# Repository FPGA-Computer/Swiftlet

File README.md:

This is a Personal Sonar System or the Visually Impaired Person for HaD 2015 Contest Entry.

Ver 0.0 Rel 0/	
Initial PCB release - first layout/non-tested

Ver 0.0 Rel 0.1/	
Initial PCB release - bugs fixed (so far) against Rel 0.0

  Eagle PCB/ Eagle CAD files
  Sketch3D/  Sketch3D model
  LTSpice/   Linear Tech Spice Simulation analog file

Hackaday project page is at 
https://hw-by-design.blogspot.com/2018/07/project-swiftlet-sonar-for-visually.html

This work is licensed under a Creative Commons Attribution-
NonCommercial-ShareAlike 4.0 International License.

The full detail of this license is available at: 
http://creativecommons.org/licenses/by-nc-sa/4.0/

Please contact me via hackaday.io for commercial inquiries.

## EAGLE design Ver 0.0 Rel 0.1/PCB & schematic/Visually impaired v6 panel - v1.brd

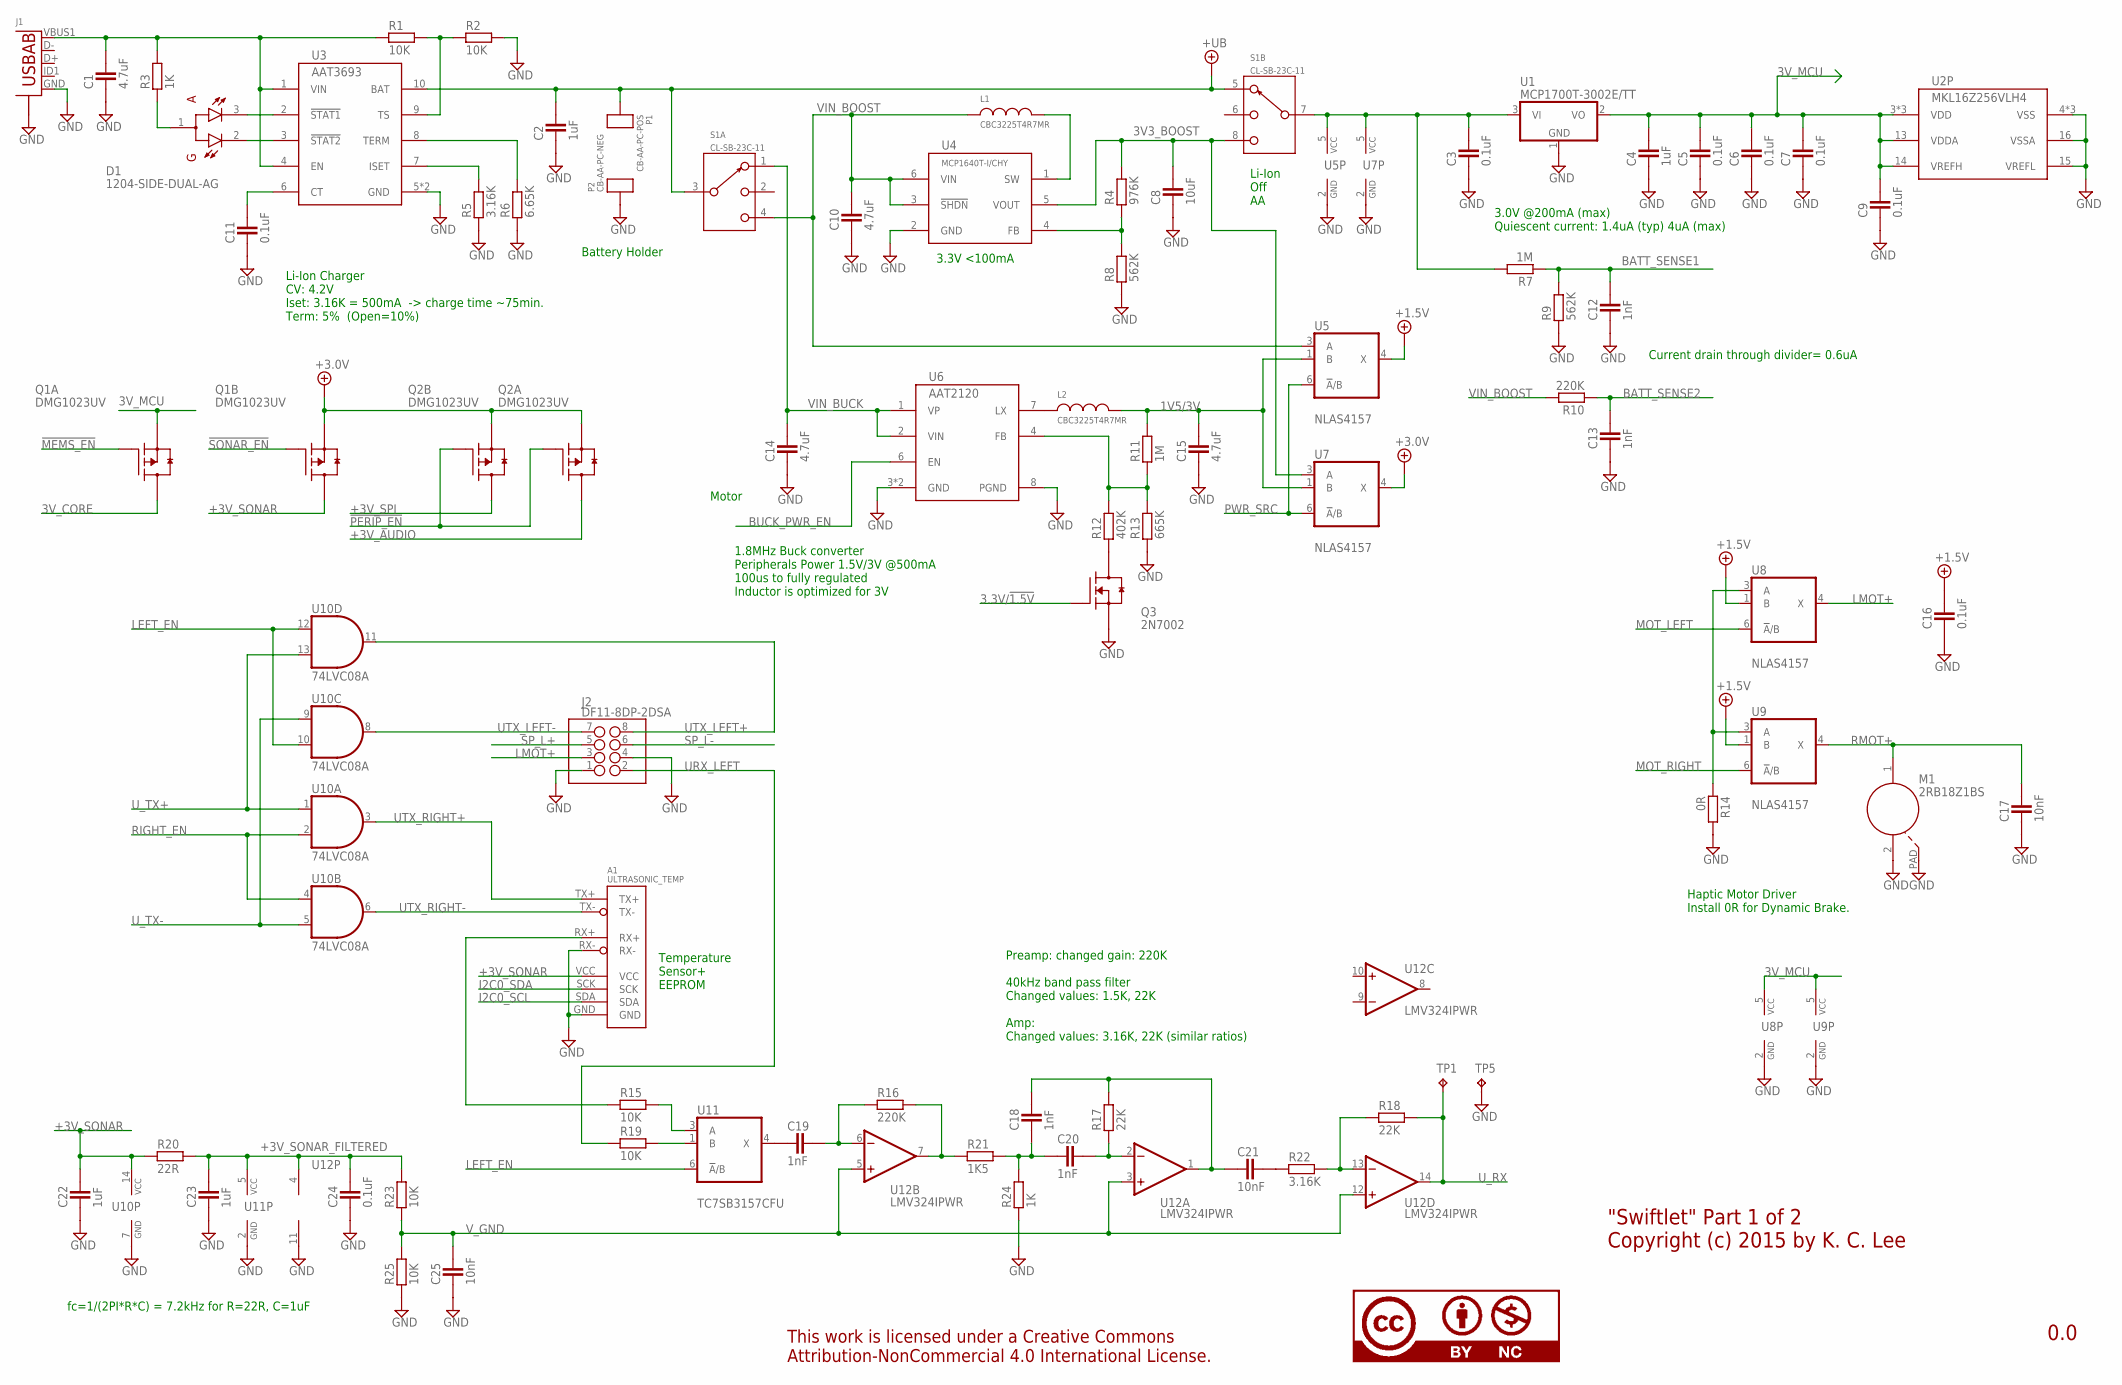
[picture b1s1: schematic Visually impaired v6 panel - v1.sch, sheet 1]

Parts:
A1: ULTRASONIC_TEMP; ULTRASONIC_ASM; PARTNO *
C1, C10, C14, C15: 4.7uF; CAPC1608X92N; PARTNO DK: 1276-2087-1-ND
C2, C22, C23: 1uF; CAPC1005X60N; PARTNO DK: 490-10435-1-ND
C3, C5, C6, C7, C9, C11, C16, C24: 0.1uF; CAPC1005X60N; PARTNO STOCK: DK 587-1227-1-ND
C4: 1uF; CAPC1608X92N; PARTNO STOCK: 1UF/10V 20% TDK
C8: 10uF; CAP2012X70N; PARTNO DK: 490-10470-1-ND
C12, C13, C18, C19, C20: 1nF; CAPC1005X60N; PARTNO DK: 490-6349-1-ND
C17, C21, C25: 10nF; CAPC1005X60N; PARTNO DK: 490-1312-1-ND
D1: 1204-SIDE-DUAL-AG; LED_1204; PARTNO STOCK
J1: USB-ABBG; USB-AB-MICRO-SMD_V03_SF; PARTNO DX: SKU134132
J2: DF11-8DP-2DSA; PARTNO DK: H10231-ND
L1, L2: CBC3225T4R7MR; INDC3225X135N; PARTNO DK: 587-1624-1-ND
M1: 2RB18Z1BS; PARTNO ALIEXPRESS
P1: CB-AA-PC-POS; PARTNO DK: CB-AA-PC-POS-ND
P2: CB-AA-PC-NEG; PARTNO DK: CB-AA-PC-NEG-ND
Q1, Q2: DMG1023UV; SOT563; PARTNO DK: DMG1023UV-7DICT-ND
Q3: 2N7002; SOT95P280X135-3N; PARTNO STOCK
R1, R2, R15, R19, R23, R25: 10K; RESC1005X40AN; PARTNO DK: 311-10.0KLRCT-ND
R3, R24: 1K; RESC1005X40AN; PARTNO DK: 311-1.00KLRCT-ND
R4: 976K; RESC1005X40AN; PARTNO DK: 1276-4289-1-ND
R5, R22: 3.16K; RESC1005X40AN; PARTNO DK: 1276-4063-1-ND
R6: 6.65K; RESC1005X40AN; PARTNO DK: 1276-4097-1-ND
R7, R11: 1M; RESC1005X40AN; PARTNO DK: 311-1.00MLRCT-ND
R8, R9: 562K; RESC1005X40AN; PARTNO DK: 1276-4268-1-ND
R10, R16: 220K; RESC1005X40AN; PARTNO DK: 311-220KLRCT-ND
R12: 402K; RESC1005X40AN; PARTNO DK: 1276-4254-1-ND
R13: 665K; RESC1005X40AN; PARTNO DK: 1276-4275-1-ND
R14: 0R; RESC1005X40AN; PARTNO DK: 311-0.0JRCT-ND
R17, R18: 22K; RESC1005X40AN; PARTNO DK: 311-22.0KLRCT-ND
R20: 22R; RESC1005X40AN; PARTNO DK: 311-22.0LRCT-ND
R21: 1K5; RESC1005X40AN; PARTNO DK: 311-1.50KLRCT-ND
S1: CL-SB-23C-11; SW-JS203011AQN; PARTNO DK: 563-1360-ND
TP1, TP5: TPTP06SQ; TP06SQ; PARTNO *
U1: MCP1700T-3002E/TT; SOT95P280X135-3N; PARTNO STOCK: MCP1700T-3002E/TTCT-ND
U2: MKL16Z256VLH4; LQFP64; PARTNO DK: MKL16Z256VLH4-ND
U3: AAT3693; TDFN-10; PARTNO DK: 863-1512-1-ND
U4: MCP1640T-I/CHY; SOT26; PARTNO DK: MCP1640T-I/CHYCT-ND
U5, U7, U8, U9: NLAS4157; DCK_R-PDSO-G6; PARTNO DK: NLAS4157DFT2GOSCT-ND
U6: AAT2120; STDFN22-8; PARTNO DK: 863-1527-1-ND
U10: 74LVC08A; TSSOP14; PARTNO DK: 296-1221-1-ND
U11: TC7SB3157CFU; DCK_R-PDSO-G6; PARTNO DK: TC7SB3157CFULFCT-ND
U12: LMV324IPWR; TSSOP14; PARTNO DK: LMV324TSG-13DICT-ND
U$1: CC100%; CC-100; PARTNO *

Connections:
1V5/3V: C15.2, L2.2, R11.2, U5.1 (B), U7.1 (B)
3.3V/!1.5V: Q3.1 (G); also elsewhere on the board
3V3_BOOST: C8.2, R4.2, S1.8 (3), U4.5 (VOUT), U7.3 (A)
3V_CORE: Q1.P$6 (D); also elsewhere on the board
3V_MCU: C4.2, C5.2, C6.2, C7.2, C9.2, Q1.P$1 (S), U1.2 (VO), U2.3 (VDD), U2.13 (VDDA), U2.14 (VREFH), U2.30 (VDD), U2.48 (VDD), U8.5 (VCC), U9.5 (VCC); also elsewhere on the board
!MEMS_EN: Q1.P$2 (G); also elsewhere on the board
!PERIP_EN: Q2.P$2 (G), Q2.P$5 (G); also elsewhere on the board
!SONAR_EN: Q1.P$5 (G); also elsewhere on the board
+1.5V: C16.2, U5.4 (X), U8.1 (B), U9.1 (B)
+3.0V: Q1.P$4 (S), Q2.P$1 (S), Q2.P$4 (S), U7.4 (X); also elsewhere on the board
+3V_AUDIO: Q2.P$6 (D); also elsewhere on the board
+3V_SONAR: A1.VCC, C22.2, Q1.P$3 (D), R20.1, U10.14 (VCC)
+3V_SONAR_FILTERED: C23.2, C24.2, R20.2, R23.2, U11.5 (VCC), U12.4 (V+)
+3V_SPI: Q2.P$3 (D); also elsewhere on the board
+UB: C2.2, P1.1, S1.3 (S), S1.5 (1), U3.10 (BAT)
BATT_SENSE1: C12.2, R7.1, R9.2; also elsewhere on the board
BATT_SENSE2: C13.2, R10.1; also elsewhere on the board
BUCK_PWR_EN: U6.6 (EN); also elsewhere on the board
GND: A1.GND, A1.RX-, C1.1, C2.1, C3.1, C4.1, C5.1, C6.1, C7.1, C8.1, C9.1, C10.1, C11.1, C12.1, C13.1, C14.1, C15.1, C16.1, C17.1, C22.1, C23.1, C24.1, C25.1, J1.GND, J1.S1 (S), J1.S2 (S), J1.S3 (S), J1.S4 (S), J2.1, J2.4, M1.2, M1.PAD, P2.1, P2.2, Q3.2 (S), R2.2, R5.1, R6.1, R8.1, R9.1, R13.1, R14.2, R24.1, R25.1, TP5.TP, U1.1 (GND), U2.4 (VSS), U2.15 (VREFL), U2.16 (VSSA), U2.31 (VSS), U2.47 (VSS), U3.5 (GND), U3.EP (GND), U4.2 (GND), U5.2 (GND), U6.3 (GND), U6.8 (PGND), U6.PAD (GND), U7.2 (GND), U8.2 (GND), U9.2 (GND), U10.7 (GND), U11.2 (GND), U12.11 (V-); also elsewhere on the board
I2C0_SCL: A1.SDA; also elsewhere on the board
I2C0_SDA: A1.SCK; also elsewhere on the board
LEFT_EN: U10.10 (I1), U10.12 (I0), U11.6 (!A!/B); also elsewhere on the board
LMOT+: J2.3, U8.4 (X)
MOT_LEFT: U8.6 (!A!/B); also elsewhere on the board
MOT_RIGHT: U9.6 (!A!/B); also elsewhere on the board
unnamed: A1.RX+, R15.1
unnamed: R14.1, U8.3 (A), U9.3 (A)
unnamed: L1.2, U4.1 (SW)
unnamed: C11.2, U3.6 (CT)
unnamed: R5.2, U3.7 (ISET)
unnamed: R6.2, U3.8 (TERM)
unnamed: D1.1 (A), R3.1
unnamed: D1.3 (C1), U3.2 (!STAT1)
unnamed: D1.2 (C2), U3.3 (!STAT2)
unnamed: C1.2, J1.VBUS1 (VBUS), R1.1, R3.2, U3.1 (VIN), U3.4 (EN)
unnamed: R1.2, R2.1, U3.9 (TS)
unnamed: C21.2, R22.1
unnamed: R19.2, U11.1 (B)
unnamed: R18.1, R22.2, U12.13 (-IN)
unnamed: C19.2, R16.1, U12.6 (-IN)
unnamed: R16.2, R21.1, U12.7 (OUT)
unnamed: C18.1, C20.1, R21.2, R24.2
unnamed: C20.2, R17.1, U12.2 (-IN)
unnamed: R15.2, U11.3 (A)
unnamed: C19.1, U11.4 (X)
unnamed: R4.1, R8.2, U4.4 (FB)
unnamed: L2.1, U6.7 (LX)
unnamed: R11.1, R12.2, R13.2, U6.4 (FB)
unnamed: Q3.3 (D), R12.1
PWR_SRC: U5.6 (!A!/B), U7.6 (!A!/B); also elsewhere on the board
RIGHT_EN: U10.2 (I1), U10.4 (I0); also elsewhere on the board
RMOT+: C17.2, M1.1, U9.4 (X)
SP_L+: J2.5; also elsewhere on the board
SP_L-: J2.6; also elsewhere on the board
URX_LEFT: J2.2, R19.1
UTX_LEFT+: J2.8, U10.11 (O)
UTX_LEFT-: J2.7, U10.8 (O)
UTX_RIGHT+: A1.TX+, U10.3 (O)
UTX_RIGHT-: A1.TX-, U10.6 (O)
U_RX: R18.2, TP1.TP, U12.14 (OUT); also elsewhere on the board
U_RX__: C18.2, C21.1, R17.2, U12.1 (OUT)
U_TX+: U10.1 (I0), U10.13 (I1); also elsewhere on the board
U_TX-: U10.5 (I1), U10.9 (I0); also elsewhere on the board
VIN_BOOST: C10.2, L1.1, R10.2, S1.4 (3), U4.3 (!SHDN), U4.6 (VIN), U5.3 (A)
VIN_BUCK: C14.2, S1.1, U6.1 (VP), U6.2 (VIN)
VIN_MCU: C3.2, R7.2, S1.7 (S), U1.3 (VI), U5.5 (VCC), U7.5 (VCC)
V_GND: C25.2, R23.1, R25.2, U12.3 (+IN), U12.5 (+IN), U12.12 (+IN)

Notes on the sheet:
Li-Ion Off AA
3.3V <100mA
Li-Ion Charger CV: 4.2V Iset: 3.16K = 500mA -> charge time ~75min. Term: 5% (Open=10%)
3.0V @200mA (max) Quiescent current: 1.4uA (typ) 4uA (max)
Motor
Battery Holder
Preamp: changed gain: 220K 40kHz band pass filter Changed values: 1.5K, 22K Amp: Changed values: 3.16K, 22K (similar ratios)
1.8MHz Buck converter Peripherals Power 1.5V/3V @500mA 100us to fully regulated Inductor is optimized for 3V
Temperature Sensor+ EEPROM
Haptic Motor Driver Install 0R for Dynamic Brake.
fc=1/(2PI*R*C) = 7.2kHz for R=22R, C=1uF
"Swiftlet" Part 1 of 2 Copyright (c) 2015 by K. C. Lee
0.0
Current drain through divider= 0.6uA

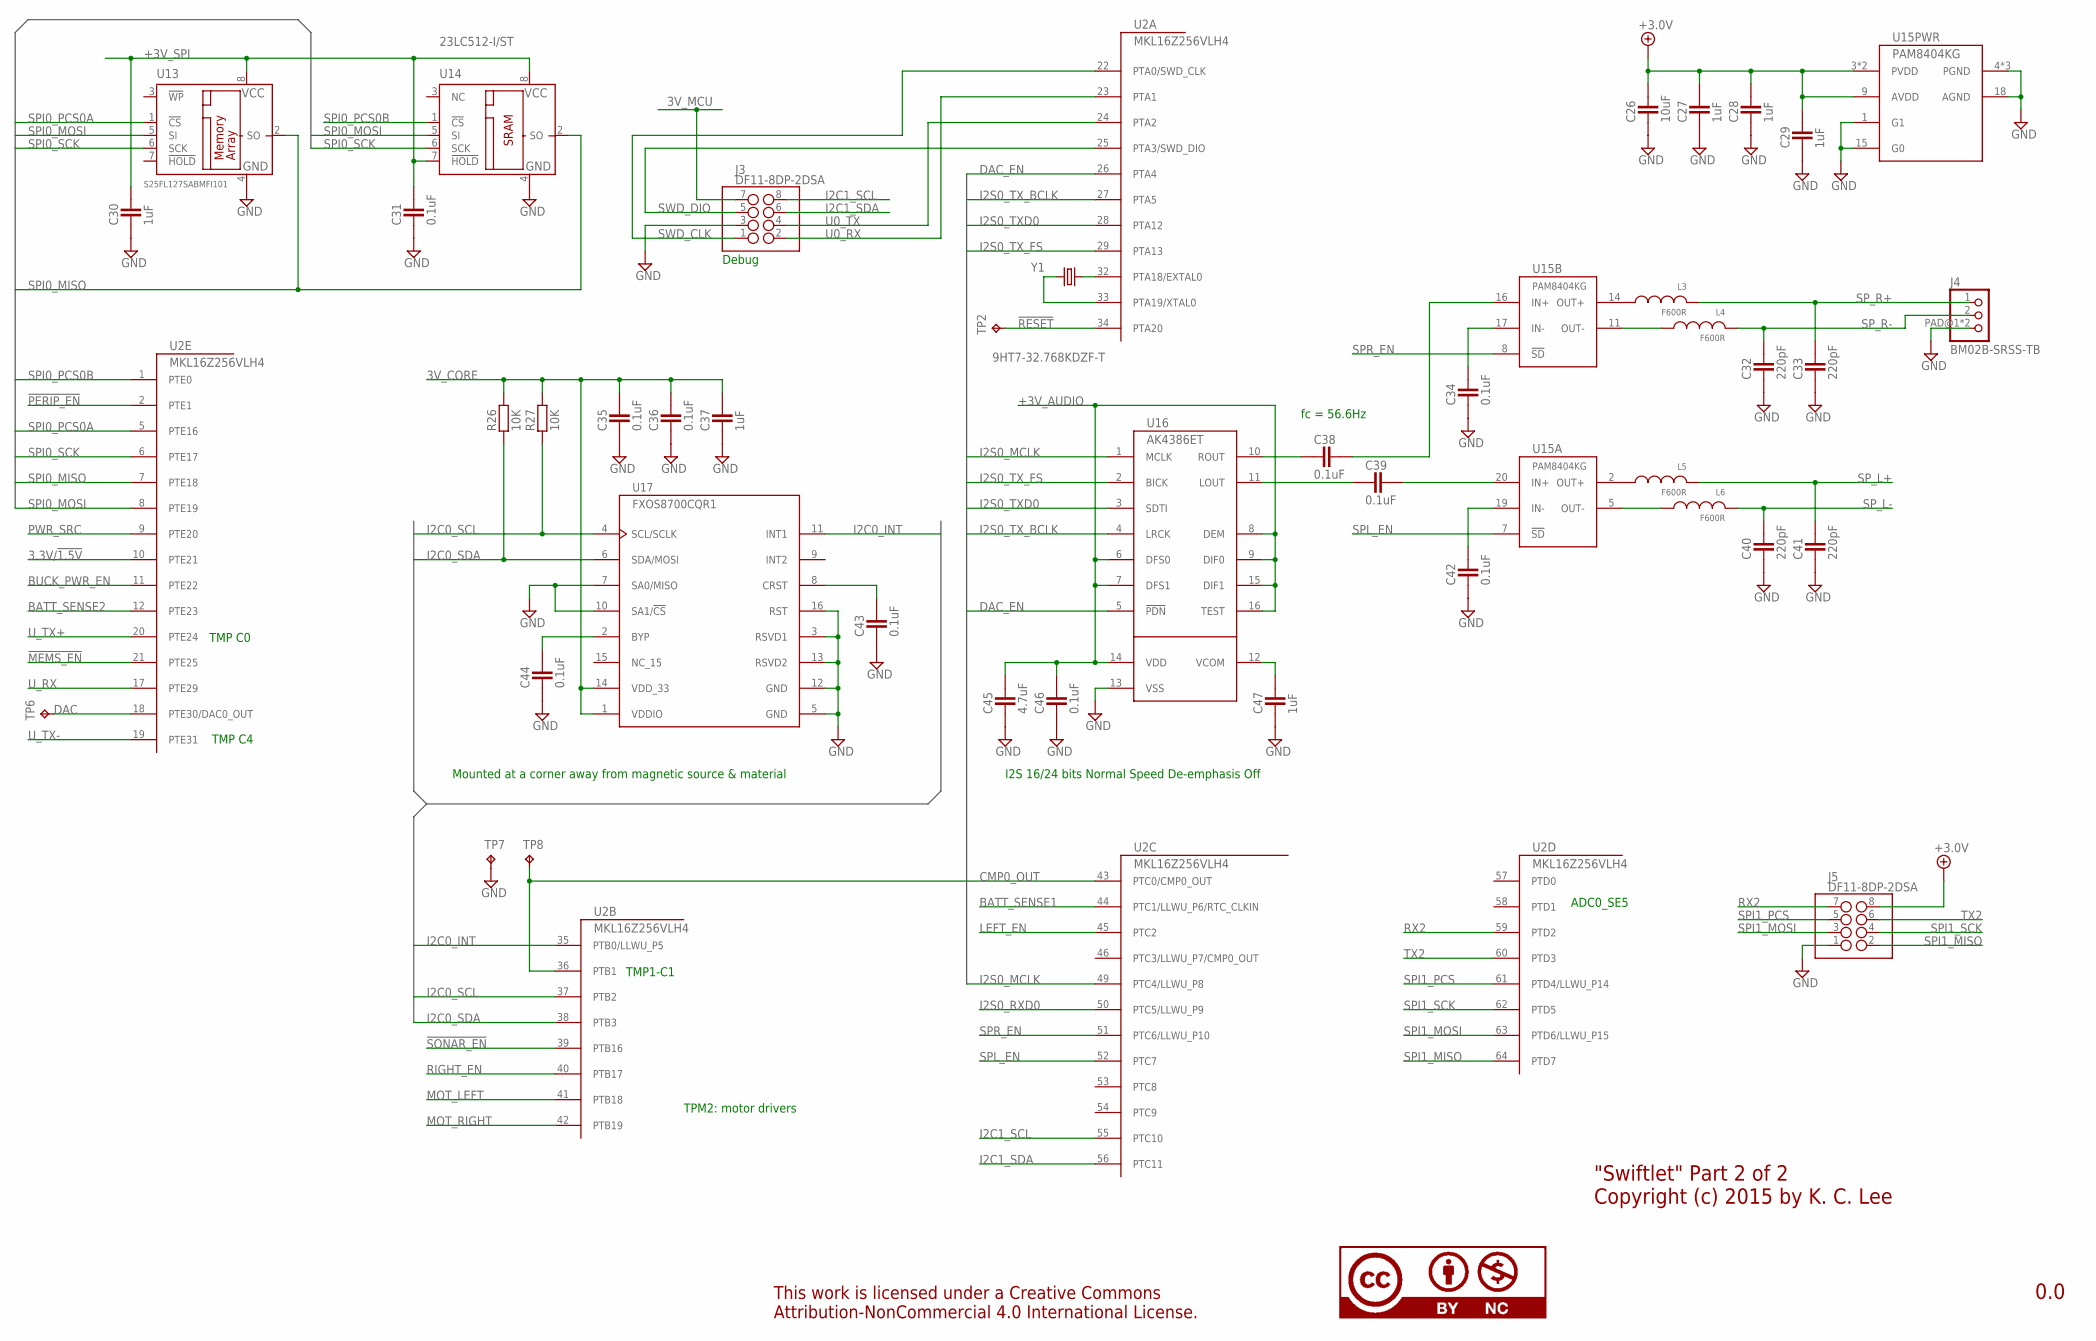
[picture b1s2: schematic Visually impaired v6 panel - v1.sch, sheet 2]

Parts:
C26: 10uF; CAP2012X70N; PARTNO DK: 490-10470-1-ND
C27, C28, C29, C30, C37, C47: 1uF; CAPC1005X60N; PARTNO DK: 490-10435-1-ND
C31, C34, C35, C36, C38, C39, C42, C43, C44, C46: 0.1uF; CAPC1005X60N; PARTNO STOCK: DK 587-1227-1-ND
C32, C33, C40, C41: 220pF; CAPC1005X60N; PARTNO DK: 1276-1531-1-ND
C45: 4.7uF; CAPC1608X92N; PARTNO DK: 1276-2087-1-ND
J3, J5: DF11-8DP-2DSA; PARTNO DK: H10231-ND
J4: BM02B-SRSS-TB; PARTNO *
L3, L4, L5, L6: F600R; INDC1005X60N; PARTNO DK: 553-2374-1-ND
R26, R27: 10K; RESC1005X40AN; PARTNO DK: 311-10.0KLRCT-ND
TP2, TP6, TP7, TP8: TPTP06SQ; TP06SQ; PARTNO *
U2: MKL16Z256VLH4; LQFP64; PARTNO DK: MKL16Z256VLH4-ND
U13: S25FL127SABMFI101; S0C008; PARTNO STOCK: DK 1274-1045-ND
U14: 23LC512-I/ST; TSSOP8; PARTNO DK: 23LC512-I/ST-ND
U15: PAM8404KG; QFN4040-20; PARTNO DK: PAM8404KGRDICT-ND
U16: AK4386ET; TSSOP16; PARTNO DK: 974-1010-1-ND
U17: FXOS8700CQR1; QFN16_0P5_3X3; PARTNO DK: FXOS8700CQR1CT-ND
U$3: CC100%; CC-100; PARTNO *
Y1: 9HT7-32.768KDZF-T; 9HT7; PARTNO DK: 887-1860-1-ND

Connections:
3.3V/!1.5V: U2.10 (PTE21); also elsewhere on the board
3V_CORE: C35.2, C36.2, C37.2, R26.2, R27.2, U17.1 (VDDIO), U17.14 (VDD_33); also elsewhere on the board
3V_MCU: J3.7; also elsewhere on the board
!MEMS_EN: U2.21 (PTE25); also elsewhere on the board
!PERIP_EN: U2.2 (PTE1); also elsewhere on the board
!RESET: TP2.TP, U2.34 (PTA20)
!SONAR_EN: U2.39 (PTB16); also elsewhere on the board
+3.0V: C26.2, C27.2, C28.2, C29.2, J5.8, U15.3 (PVDD), U15.9 (AVDD), U15.13 (PVDD); also elsewhere on the board
+3V_AUDIO: C45.2, C46.2, U16.6 (DFS0), U16.7 (DFS1), U16.8 (DEM), U16.9 (DIF0), U16.14 (VDD), U16.15 (DIF1), U16.16 (TEST); also elsewhere on the board
+3V_SPI: C30.2, C31.2, U13.8 (VCC), U14.7 (!HOLD), U14.8 (VCC); also elsewhere on the board
BATT_SENSE1: U2.44 (PTC1/LLWU_P6/RTC_CLKIN); also elsewhere on the board
BATT_SENSE2: U2.12 (PTE23); also elsewhere on the board
BUCK_PWR_EN: U2.11 (PTE22); also elsewhere on the board
BYP: C44.2, U17.2 (BYP)
CMP0_OUT: TP8.TP, U2.36 (PTB1), U2.43 (PTC0/CMP0_OUT)
CRST: C43.2, U17.8 (CRST)
DAC: TP6.TP, U2.18 (PTE30/DAC0_OUT)
DAC_EN: U2.26 (PTA4), U16.5 (!PDN)
GND: C26.1, C27.1, C28.1, C29.1, C30.1, C31.1, C32.1, C33.1, C34.1, C35.1, C36.1, C37.1, C40.1, C41.1, C42.1, C43.1, C44.1, C45.1, C46.1, C47.1, J3.3, J4.PAD@1 (3), J4.PAD@2 (3), J5.1, TP7.TP, U13.4 (GND), U14.4 (GND), U15.1 (G1), U15.4 (PGND), U15.12 (PGND), U15.15 (G0), U15.18 (AGND), U15.PAD (PGND), U16.13 (VSS), U17.3 (RSVD1), U17.5 (GND), U17.7 (SA0/MISO), U17.10 (SA1/!CS), U17.12 (GND), U17.13 (RSVD2), U17.16 (RST); also elsewhere on the board
I2C0_INT: U2.35 (PTB0/LLWU_P5), U17.11 (INT1)
I2C0_SCL: R27.1, U2.37 (PTB2), U17.4 (SCL/SCLK); also elsewhere on the board
I2C0_SDA: R26.1, U2.38 (PTB3), U17.6 (SDA/MOSI); also elsewhere on the board
I2C1_SCL: J3.8, U2.55 (PTC10)
I2C1_SDA: J3.6, U2.56 (PTC11)
I2S0_MCLK: U2.49 (PTC4/LLWU_P8), U16.1 (MCLK)
I2S0_RXD0: U2.50 (PTC5/LLWU_P9)
I2S0_TXD0: U2.28 (PTA12), U16.3 (SDTI)
I2S0_TX_BCLK: U2.27 (PTA5), U16.4 (LRCK)
I2S0_TX_FS: U2.29 (PTA13), U16.2 (BICK)
LEFT_EN: U2.45 (PTC2); also elsewhere on the board
MOT_LEFT: U2.41 (PTB18); also elsewhere on the board
MOT_RIGHT: U2.42 (PTB19); also elsewhere on the board
unnamed: U2.32 (PTA18/EXTAL0), Y1.1
unnamed: U2.33 (PTA19/XTAL0), Y1.4 (2)
unnamed: C34.2, U15.17 (IN-)
unnamed: C47.2, U16.12 (VCOM)
unnamed: C42.2, U15.19 (IN-)
unnamed: C38.1, U16.10 (ROUT)
unnamed: C38.2, U15.16 (IN+)
unnamed: C39.1, U16.11 (LOUT)
unnamed: C39.2, U15.20 (IN+)
unnamed: L3.2, U15.14 (OUT+)
unnamed: L4.2, U15.11 (OUT-)
unnamed: L5.2, U15.2 (OUT+)
unnamed: L6.2, U15.5 (OUT-)
PWR_SRC: U2.9 (PTE20); also elsewhere on the board
RIGHT_EN: U2.40 (PTB17); also elsewhere on the board
RX2: J5.7, U2.59 (PTD2)
SPI0_MISO: U2.7 (PTE18), U13.2 (SO), U14.2 (SO)
SPI0_MOSI: U2.8 (PTE19), U13.5 (SI), U14.5 (SI)
SPI0_PCS0A: U2.5 (PTE16), U13.1 (!CS)
SPI0_PCS0B: U2.1 (PTE0), U14.1 (!CS)
SPI0_SCK: U2.6 (PTE17), U13.6 (SCK), U14.6 (SCK)
SPI1_MISO: J5.2, U2.64 (PTD7)
SPI1_MOSI: J5.3, U2.63 (PTD6/LLWU_P15)
SPI1_PCS: J5.5, U2.61 (PTD4/LLWU_P14)
SPI1_SCK: J5.4, U2.62 (PTD5)
SPL_EN: U2.52 (PTC7), U15.7 (!SD)
SPR_EN: U2.51 (PTC6/LLWU_P10), U15.8 (!SD)
SP_L+: C41.2, L5.1; also elsewhere on the board
SP_L-: C40.2, L6.1; also elsewhere on the board
SP_R+: C33.2, J4.1, L3.1
SP_R-: C32.2, J4.2, L4.1
SWD_CLK: J3.1, U2.22 (PTA0/SWD_CLK)
SWD_DIO: J3.5, U2.25 (PTA3/SWD_DIO)
TX2: J5.6, U2.60 (PTD3)
U0_RX: J3.2, U2.23 (PTA1)
U0_TX: J3.4, U2.24 (PTA2)
U_RX: U2.17 (PTE29); also elsewhere on the board
U_TX+: U2.20 (PTE24); also elsewhere on the board
U_TX-: U2.19 (PTE31); also elsewhere on the board

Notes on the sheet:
TPM2: motor drivers
ADC0_SE5
I2S 16/24 bits Normal Speed De-emphasis Off
Mounted at a corner away from magnetic source & material
TMP C0
TMP C4
TMP1-C1
Debug
fc = 56.6Hz
"Swiftlet" Part 2 of 2 Copyright (c) 2015 by K. C. Lee
0.0

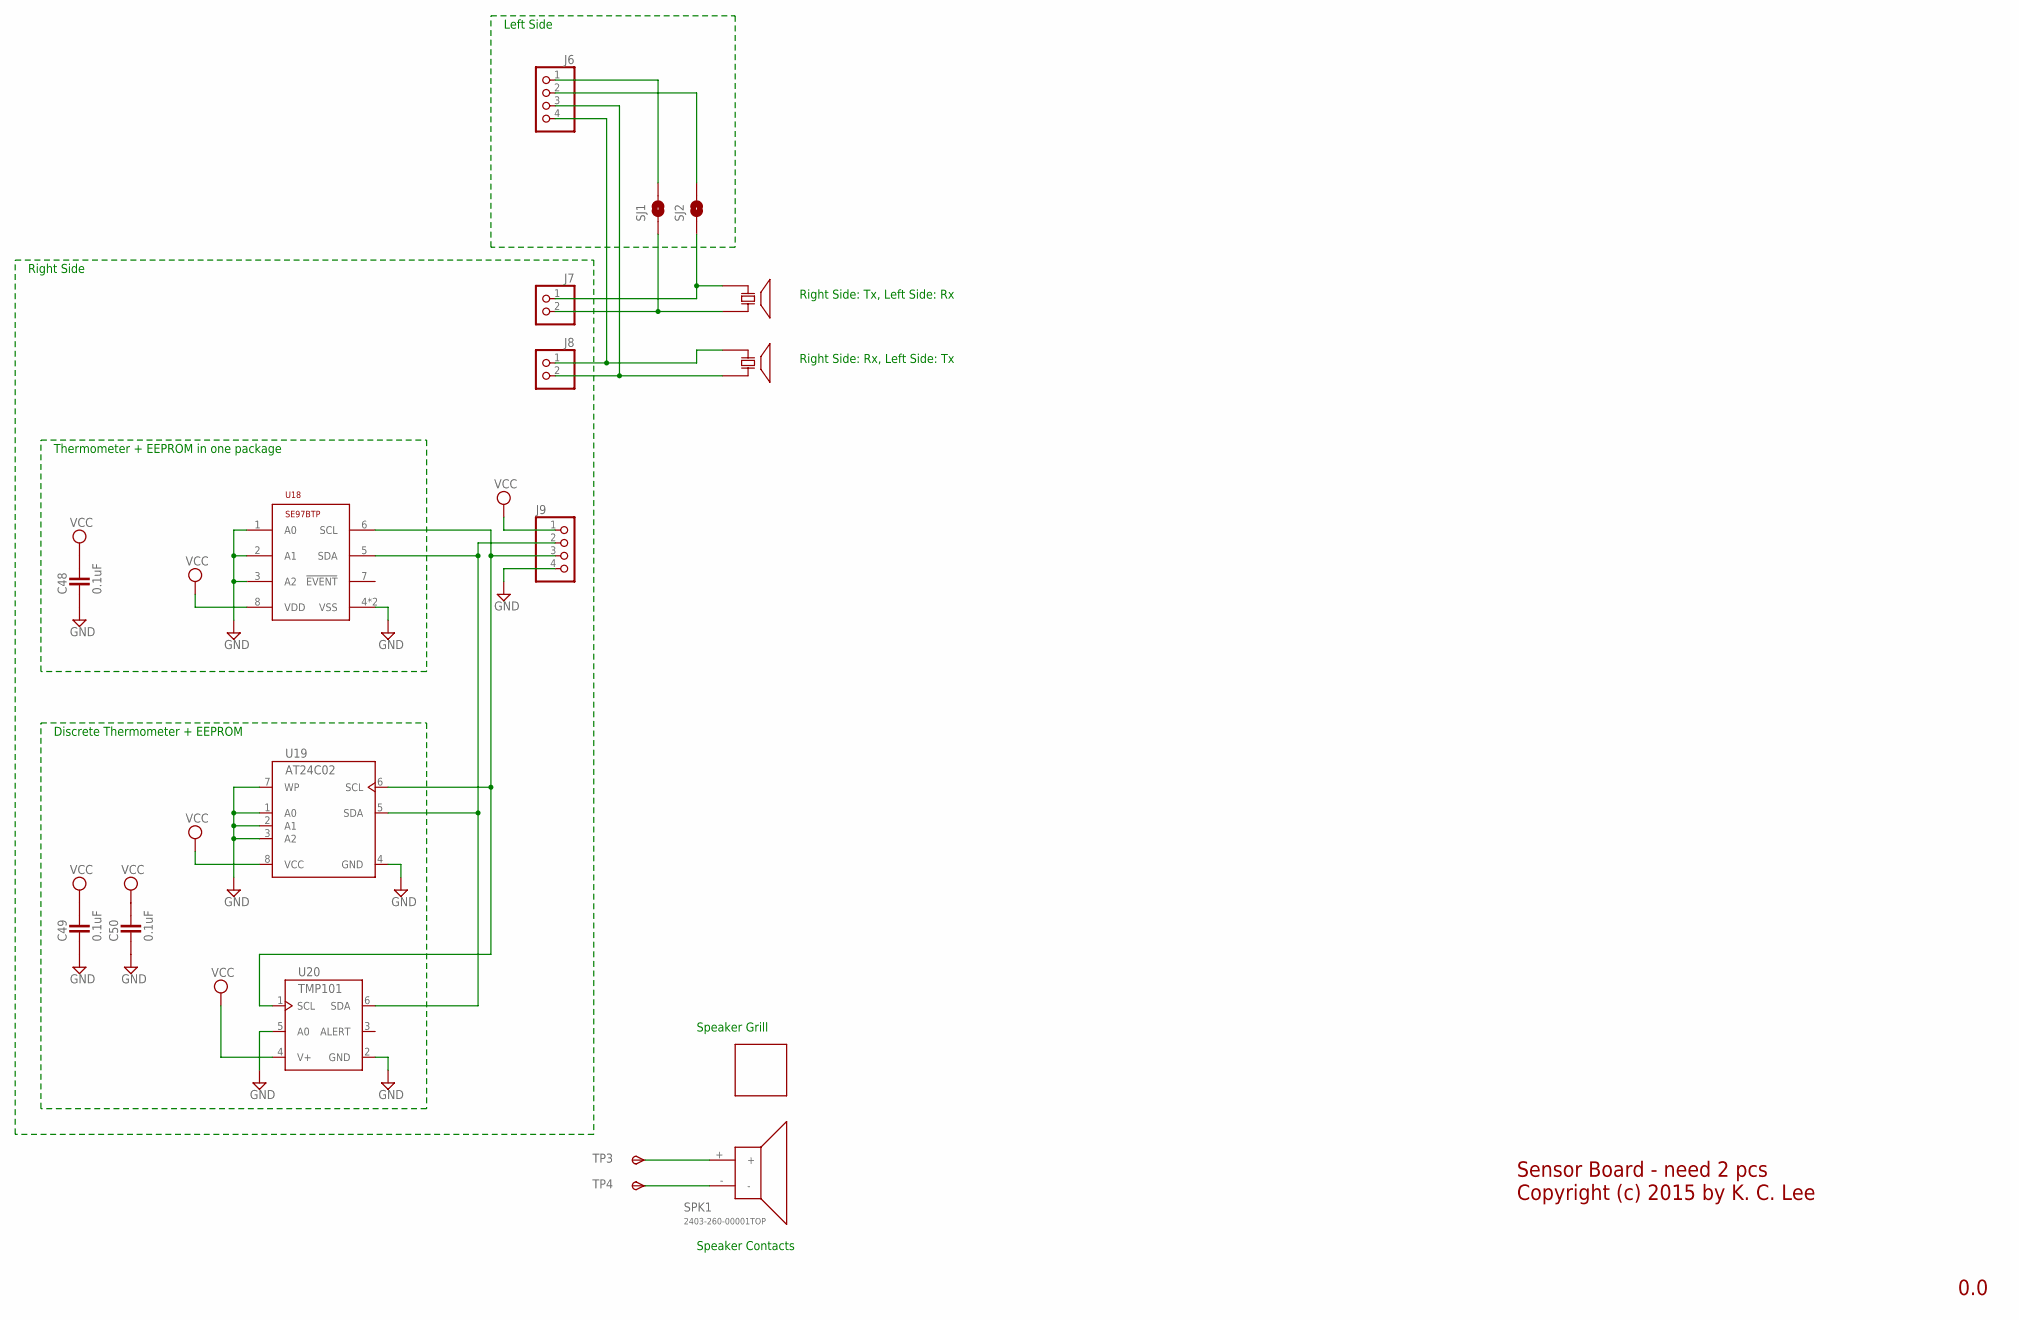
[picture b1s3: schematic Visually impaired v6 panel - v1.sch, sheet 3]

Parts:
C48, C49, C50: 0.1uF; CAPC1005X60N; PARTNO STOCK: DK 587-1227-1-ND
GRILL1: 2403-260-00001-GRILL; 24030269-00001-GRILL; PARTNO *
J6, J9: PINHD-1X4_2.54_R; 1X04R; PARTNO *
J7, J8: PINHD-1X2_2.54; 1X02; PARTNO *
SJ1, SJ2: SOLDERJUMPERNO; SJ_2S-NO; PARTNO *
SPK1: 2403-260-00001TOP; 2403-269-00001; PARTNO *
T1, T2: TCT40-16T; TCT40-16; PARTNO *
TP3, TP4: TPSTP20SQ; TP20SQ; PARTNO *
U18: SE97BTP; SOT1069-2; PARTNO *
U19: AT24C02; TSSOP8; PARTNO *
U20: TMP101; SOT26; PARTNO *

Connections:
GND: C48.1, C49.1, C50.1, J9.4, U18.1 (A0), U18.2 (A1), U18.3 (A2), U18.4 (VSS), U18.PAD (VSS), U19.1 (A0), U19.2 (A1), U19.3 (A2), U19.4 (GND), U19.7 (WP), U20.2 (GND), U20.5 (A0); also elsewhere on the board
unnamed: J6.2, SJ2.2
unnamed: J7.2, SJ1.1, T1.P$2
unnamed: J9.2, U18.5 (SDA), U19.5 (SDA), U20.6 (SDA)
unnamed: J9.3, U18.6 (SCL), U19.6 (SCL), U20.1 (SCL)
unnamed: J6.4, J8.1, T2.P$1
unnamed: J6.3, J8.2, T2.P$2
unnamed: J6.1, SJ1.2
unnamed: J7.1, SJ2.1, T1.P$1
unnamed: SPK1.+, TP3.TP
unnamed: SPK1.-, TP4.TP
VCC: C48.2, C49.2, C50.2, J9.1, U18.8 (VDD), U19.8 (VCC), U20.4 (V+)

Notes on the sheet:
Thermometer + EEPROM in one package
Discrete Thermometer + EEPROM
Left Side
Right Side
Right Side: Tx, Left Side: Rx
Right Side: Rx, Left Side: Tx
Sensor Board - need 2 pcs Copyright (c) 2015 by K. C. Lee
Speaker Grill
Speaker Contacts
0.0

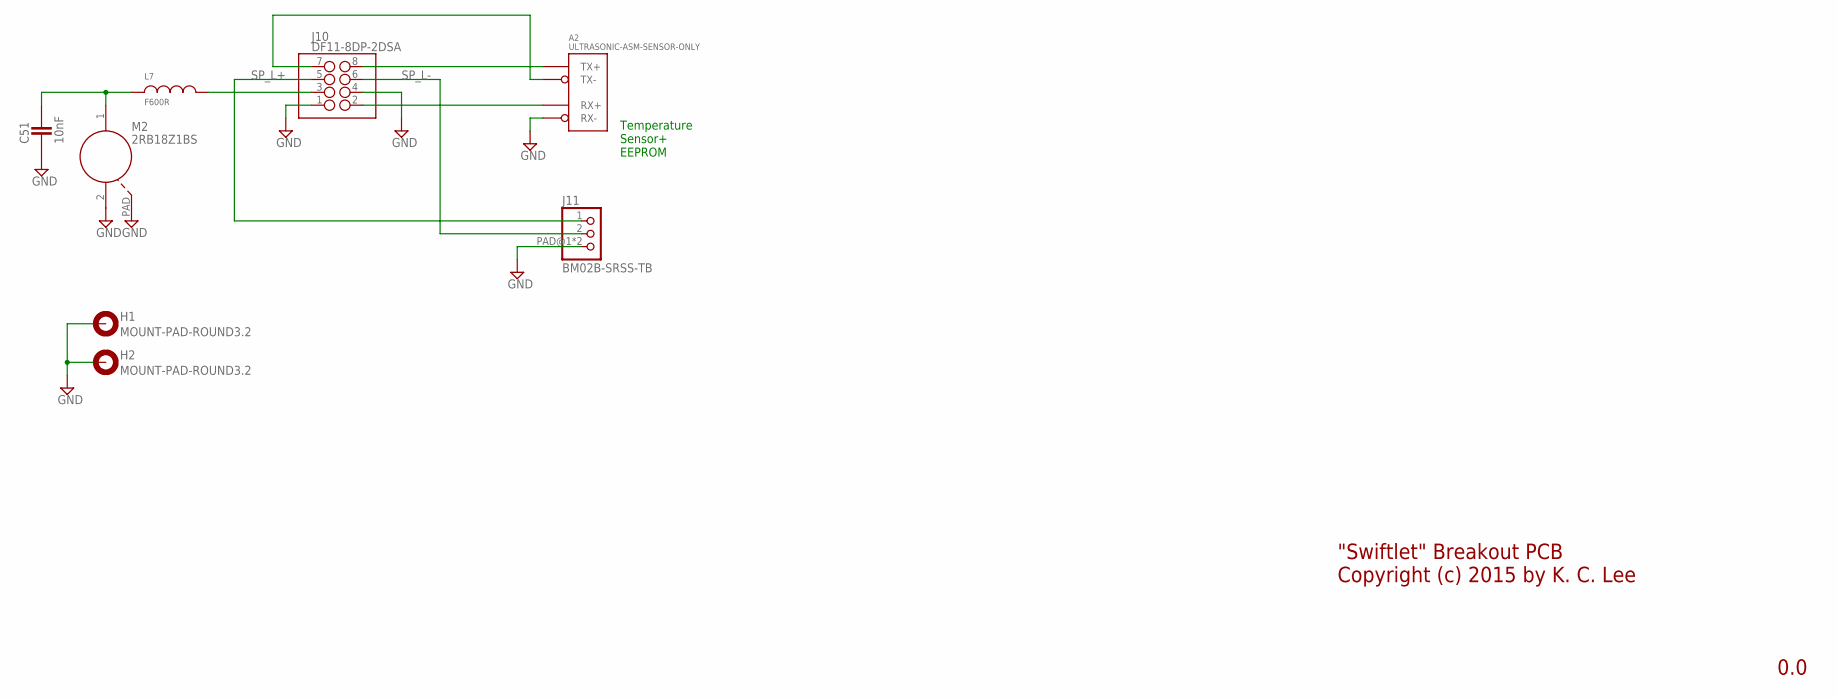
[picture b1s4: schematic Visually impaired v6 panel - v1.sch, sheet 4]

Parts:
A2: ULTRASONIC-ASM-SENSOR-ONLY; ULTRASONIC-SENSOR-ONLY; PARTNO *
C51: 10nF; CAPC1005X60N; PARTNO DK: 490-1312-1-ND
H1, H2: MOUNT-PAD-ROUND3.2; 3,2-PAD; PARTNO *
J10: DF11-8DP-2DSA; PARTNO DK: H10231-ND
J11: BM02B-SRSS-TB; PARTNO *
L7: F600R; INDC1005X60N; PARTNO DK: 553-2374-1-ND
M2: 2RB18Z1BS; PARTNO ALIEXPRESS

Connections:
GND: A2.TX+ (RX-), C51.1, H1.B3,2, H2.B3,2, J10.1, J10.4, J11.PAD@1 (3), J11.PAD@2 (3), M2.2, M2.PAD; also elsewhere on the board
LMOT+1: C51.2, L7.1, M2.1
unnamed: A2.RX+ (TX-), J10.7
unnamed: A2.TX- (RX+), J10.2
unnamed: J10.3, L7.2
SP_L+: J10.5, J11.1; also elsewhere on the board
SP_L-: J10.6, J11.2; also elsewhere on the board
UTX_RIGHT+1: A2.RX- (TX+), J10.8

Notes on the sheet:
Temperature Sensor+ EEPROM
"Swiftlet" Breakout PCB Copyright (c) 2015 by K. C. Lee
0.0

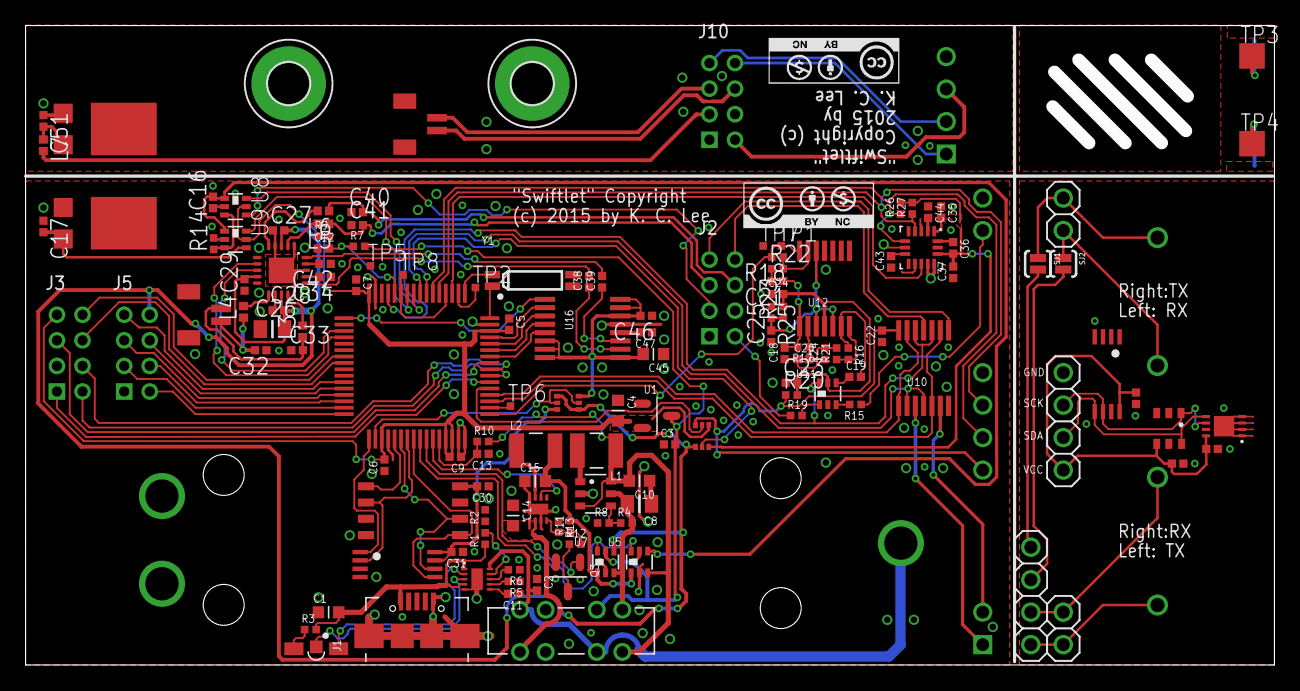
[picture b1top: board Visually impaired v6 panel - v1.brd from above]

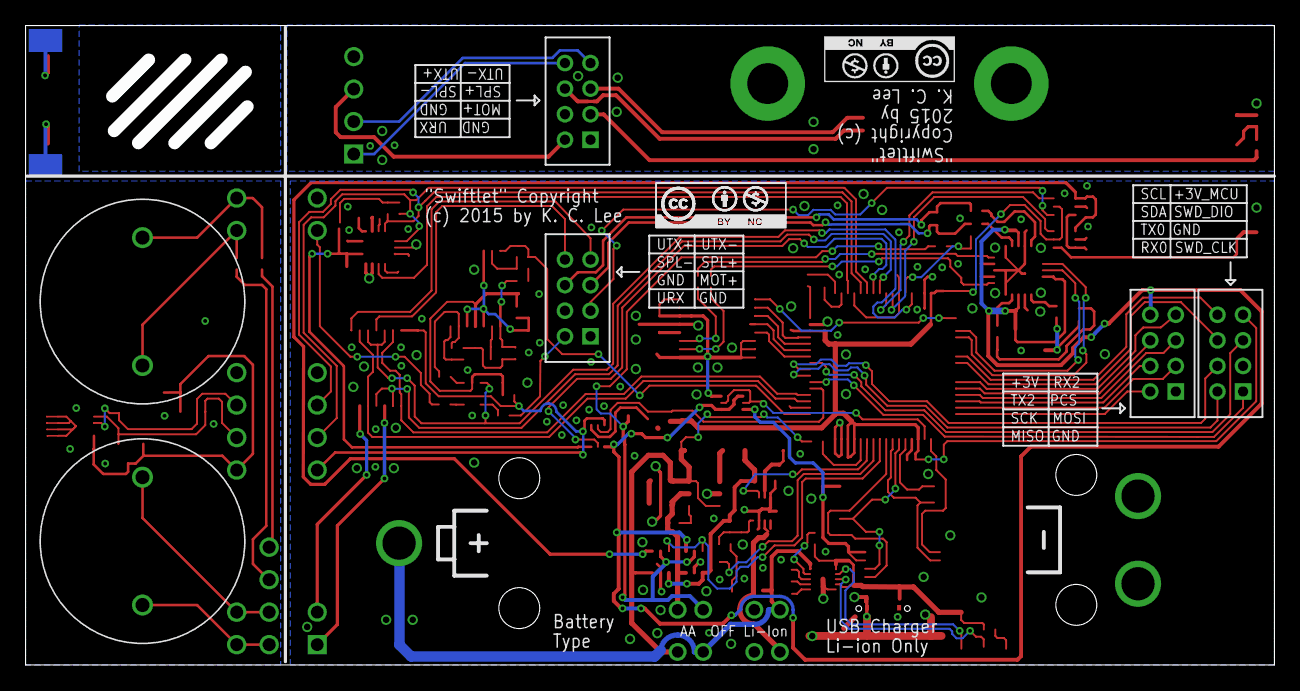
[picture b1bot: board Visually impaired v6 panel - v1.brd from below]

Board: 2 copper layers, 96.7 x 49.0 mm, 149 parts (6 on the bottom side), 128 nets.

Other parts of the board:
U$2, U$4, U$6: CC100%; CC-100

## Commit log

2015-07-25 cleanup
2015-07-25 Added printables
2015-09-11 Minor bug fixes - opamp swap & value changes
2015-09-11 Rel 0.1 directory organization
2015-09-12 Components consolidation & OM
2015-09-21 Add sonar samples
2018-07-29 New hosting site - ditching hackaday.io

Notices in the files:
parts and their libraries:
SparkFun-Passives: Licensing: Creative Commons ShareAlike 4.0 International - https://creativecommons.org/licenses/by-sa/4.0
Misc logo: Attribution-NonCommercial 4.0 International License.
